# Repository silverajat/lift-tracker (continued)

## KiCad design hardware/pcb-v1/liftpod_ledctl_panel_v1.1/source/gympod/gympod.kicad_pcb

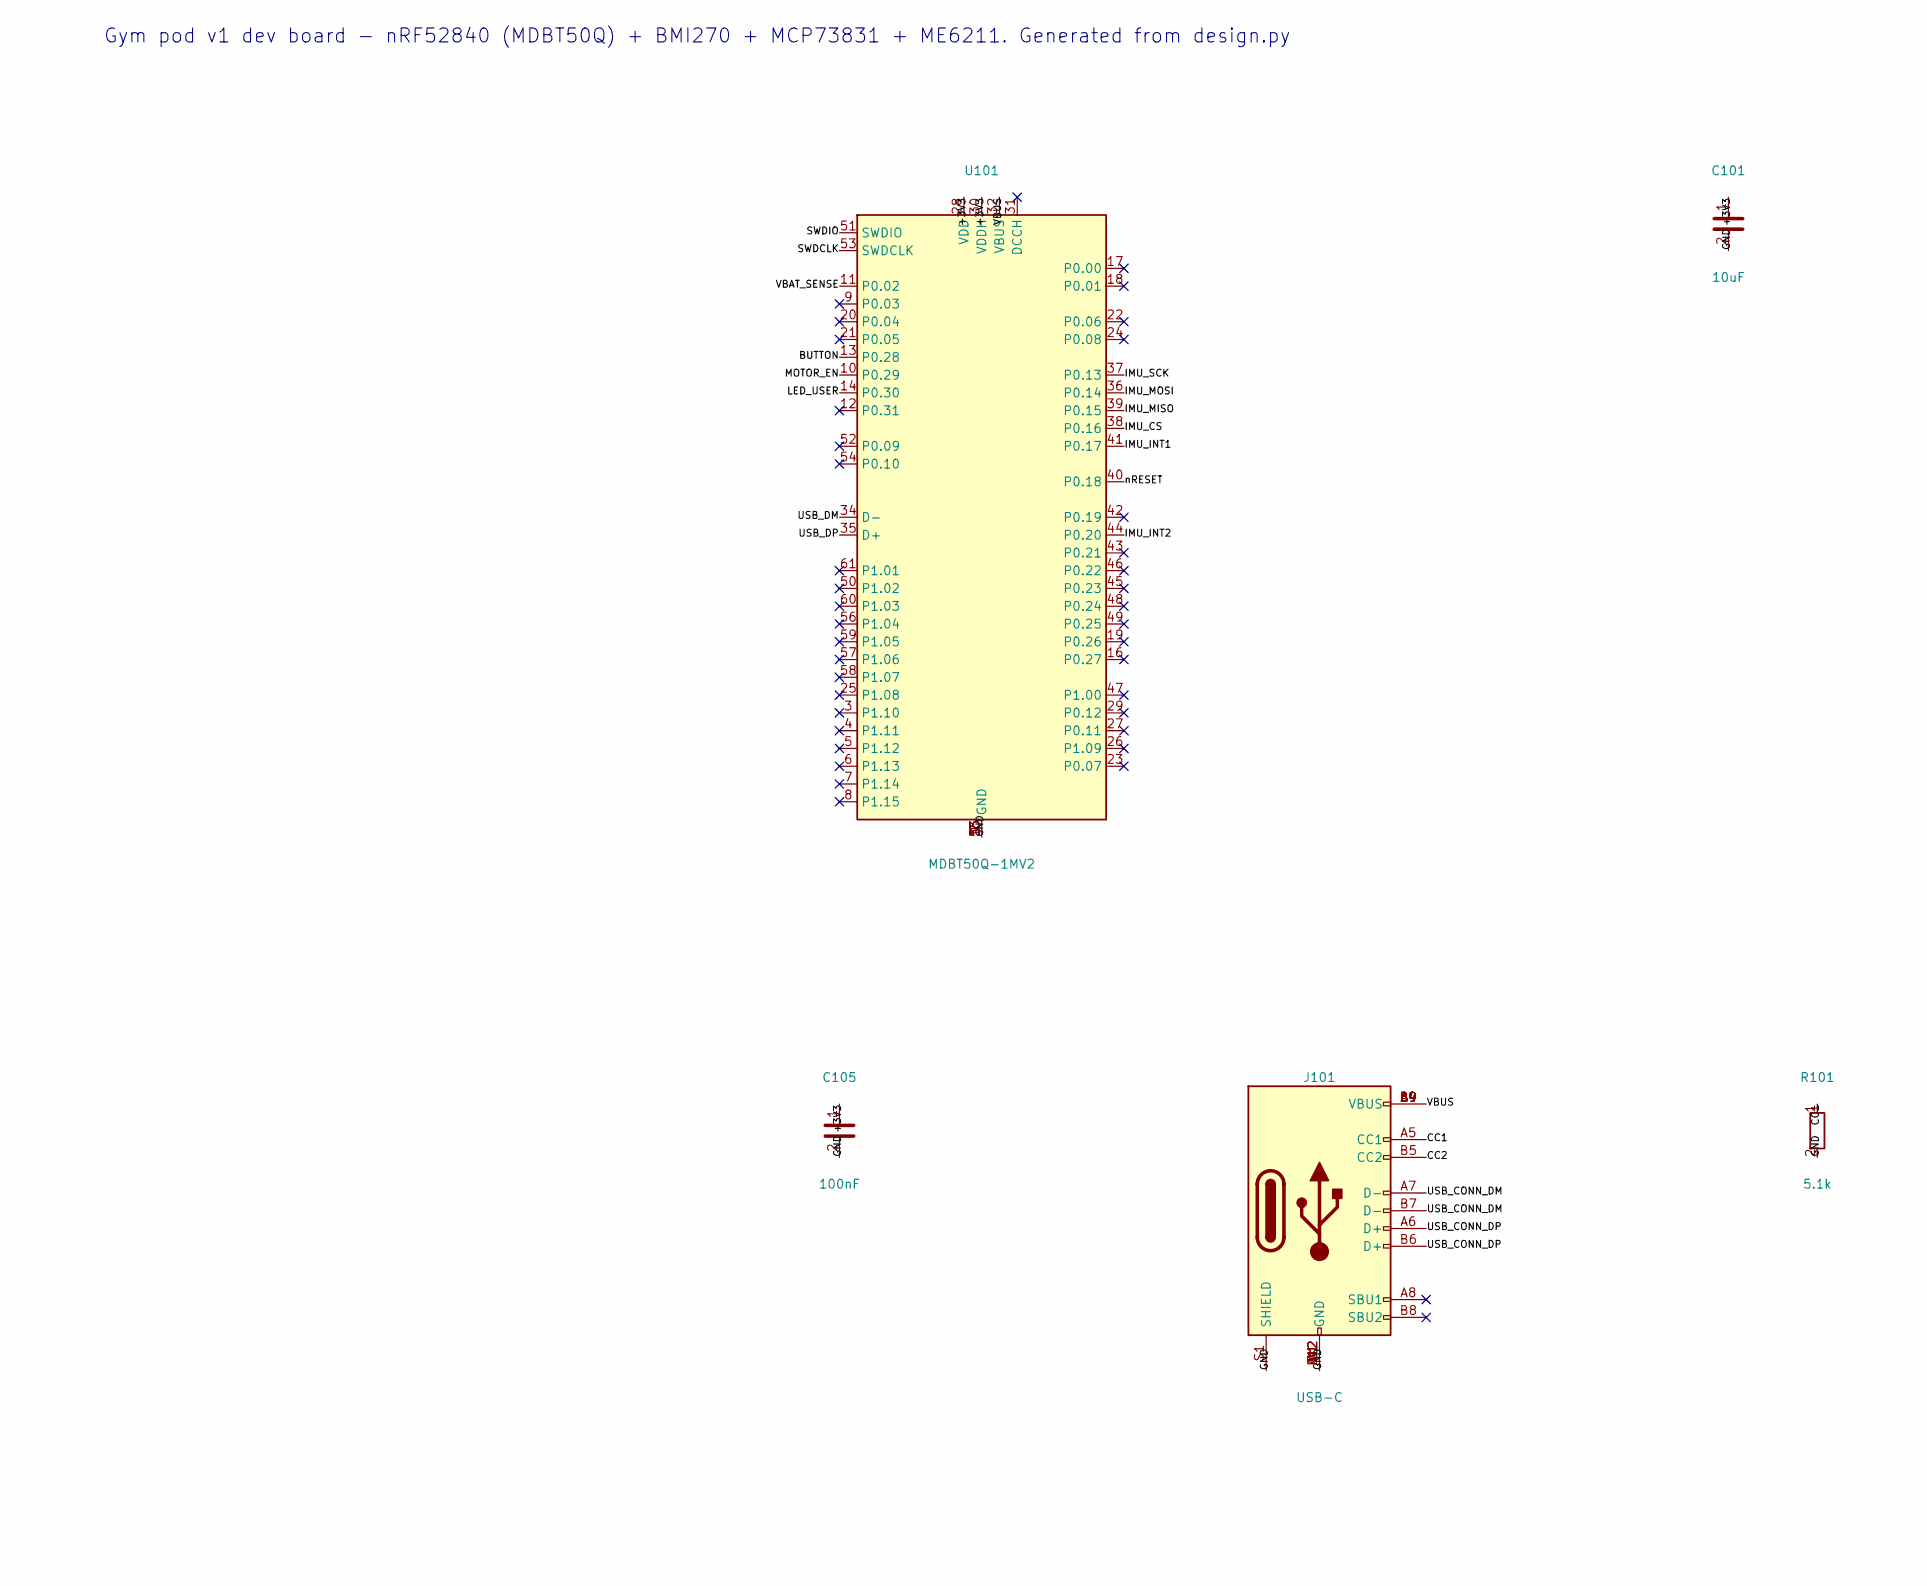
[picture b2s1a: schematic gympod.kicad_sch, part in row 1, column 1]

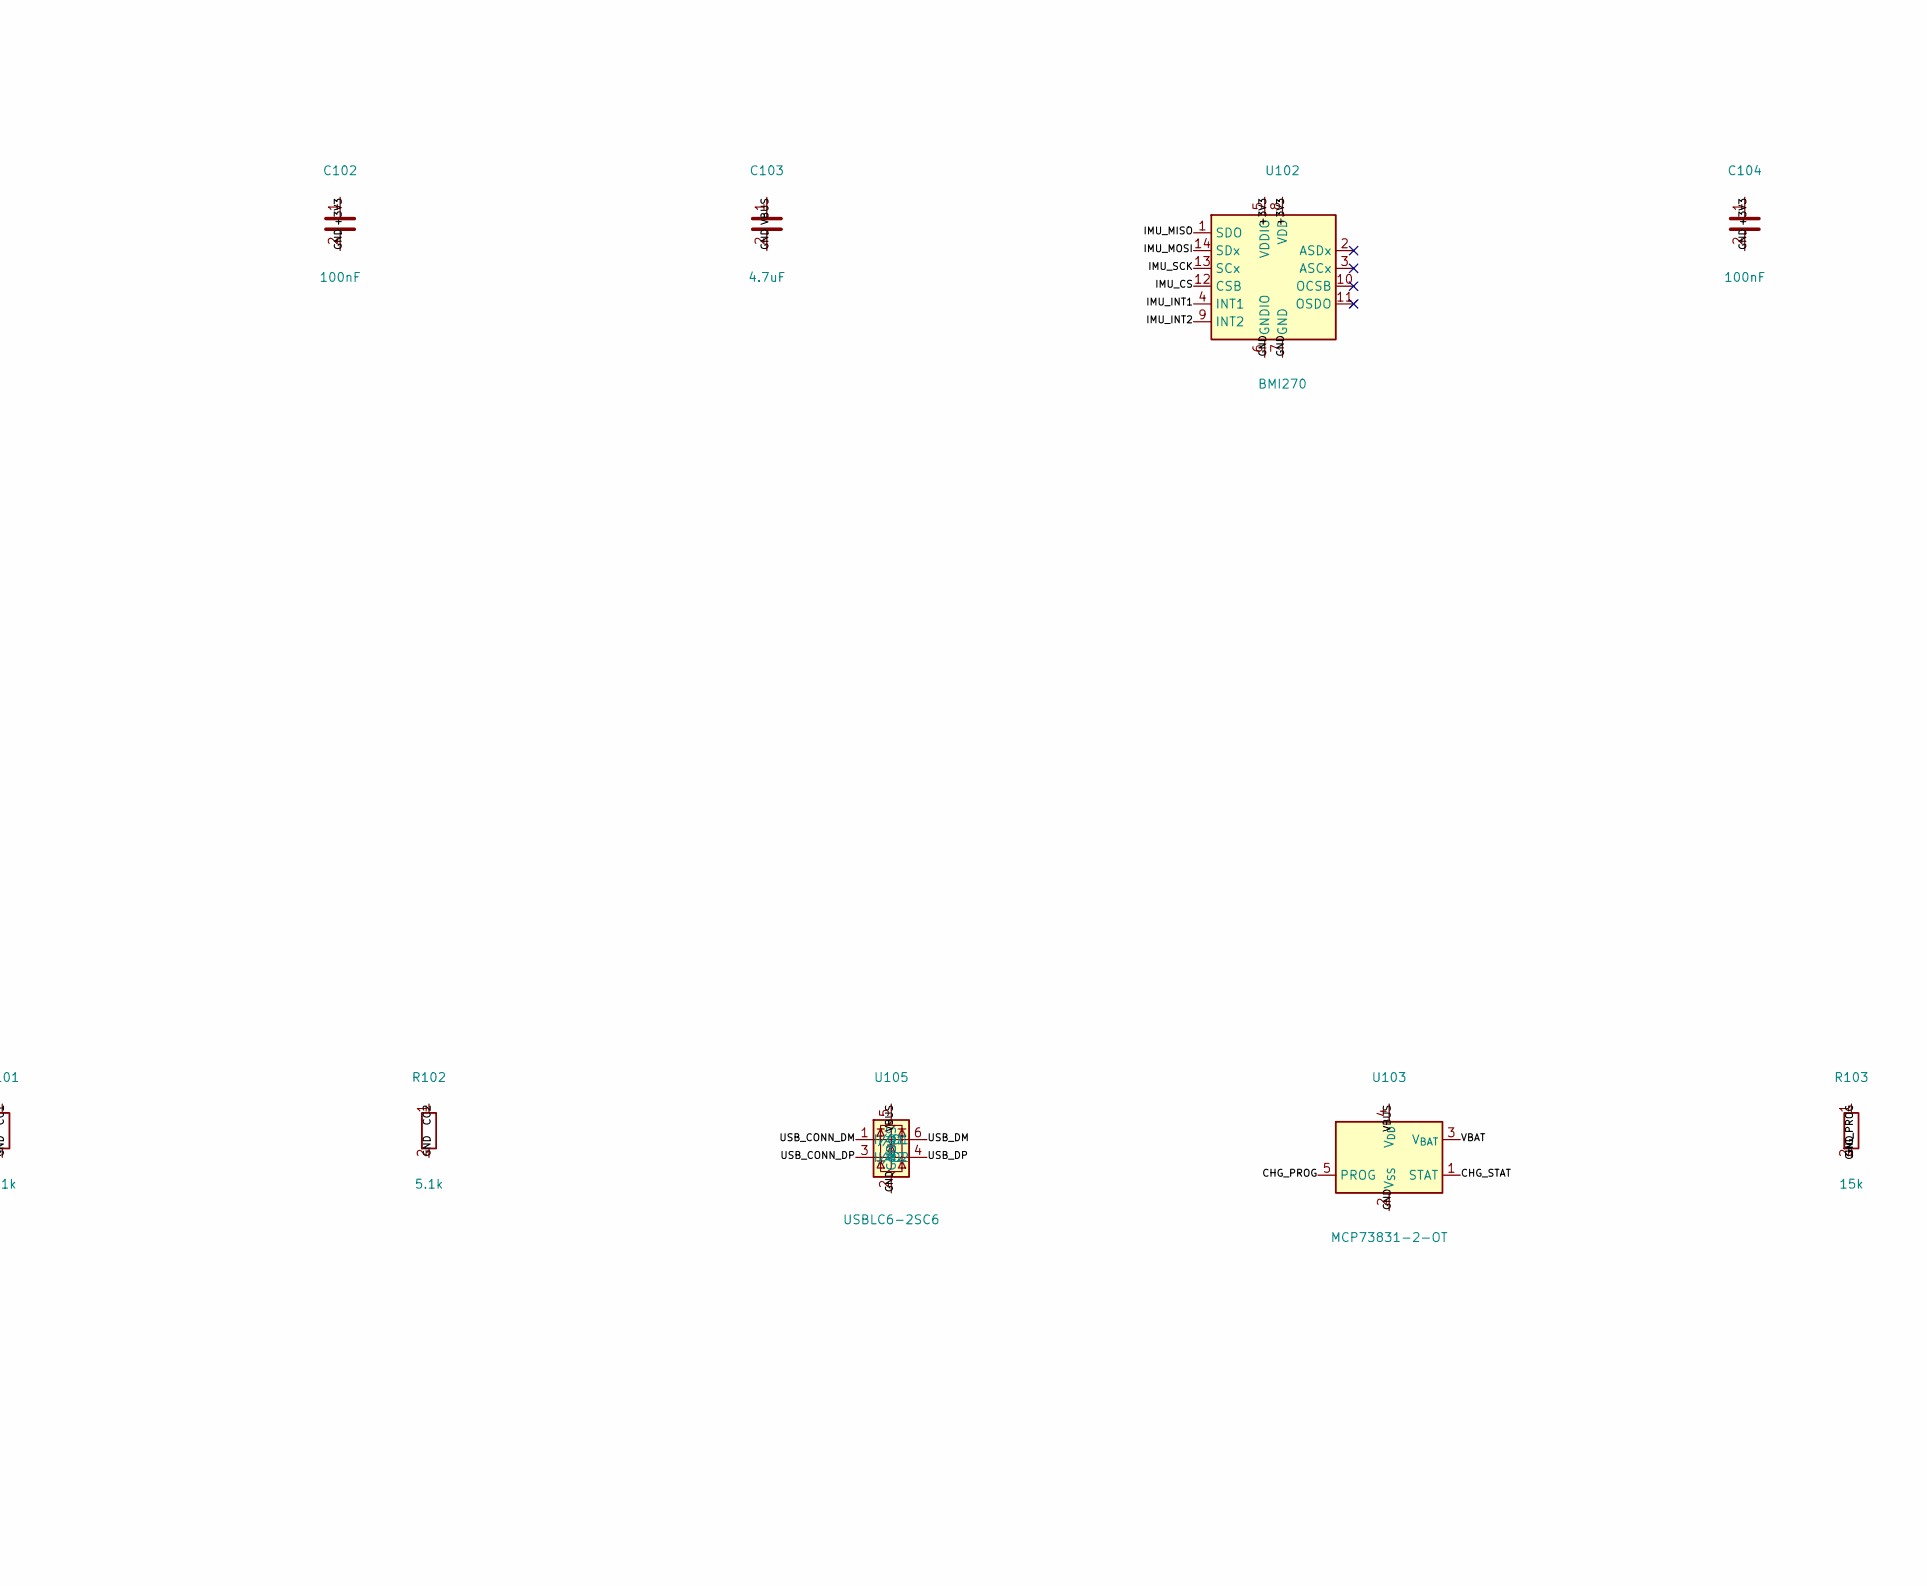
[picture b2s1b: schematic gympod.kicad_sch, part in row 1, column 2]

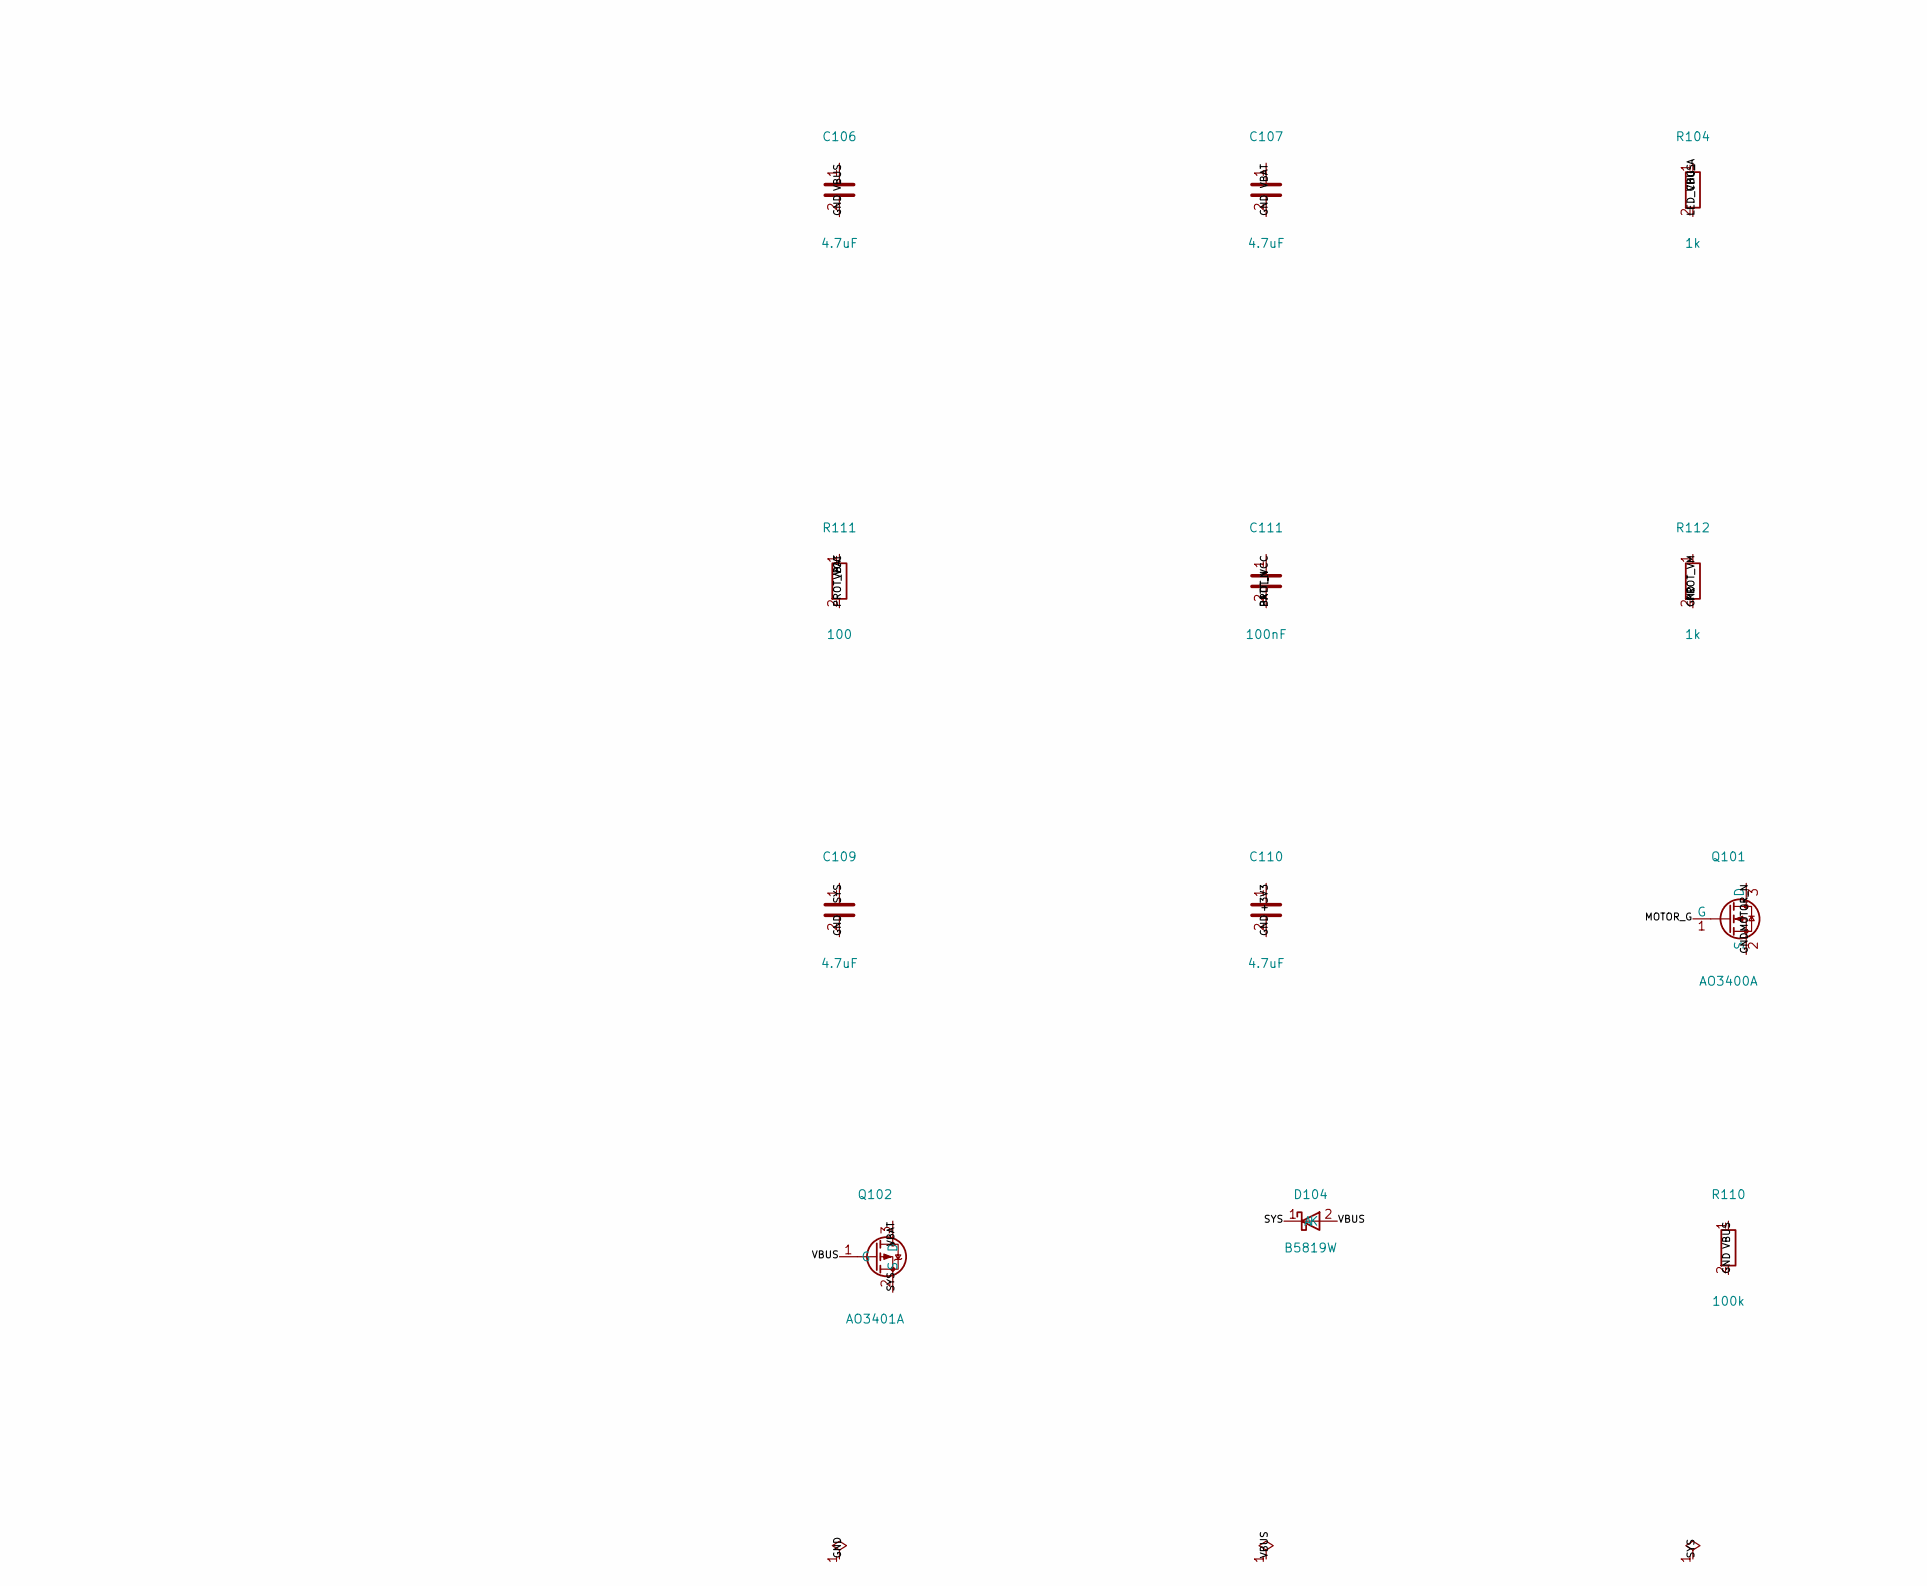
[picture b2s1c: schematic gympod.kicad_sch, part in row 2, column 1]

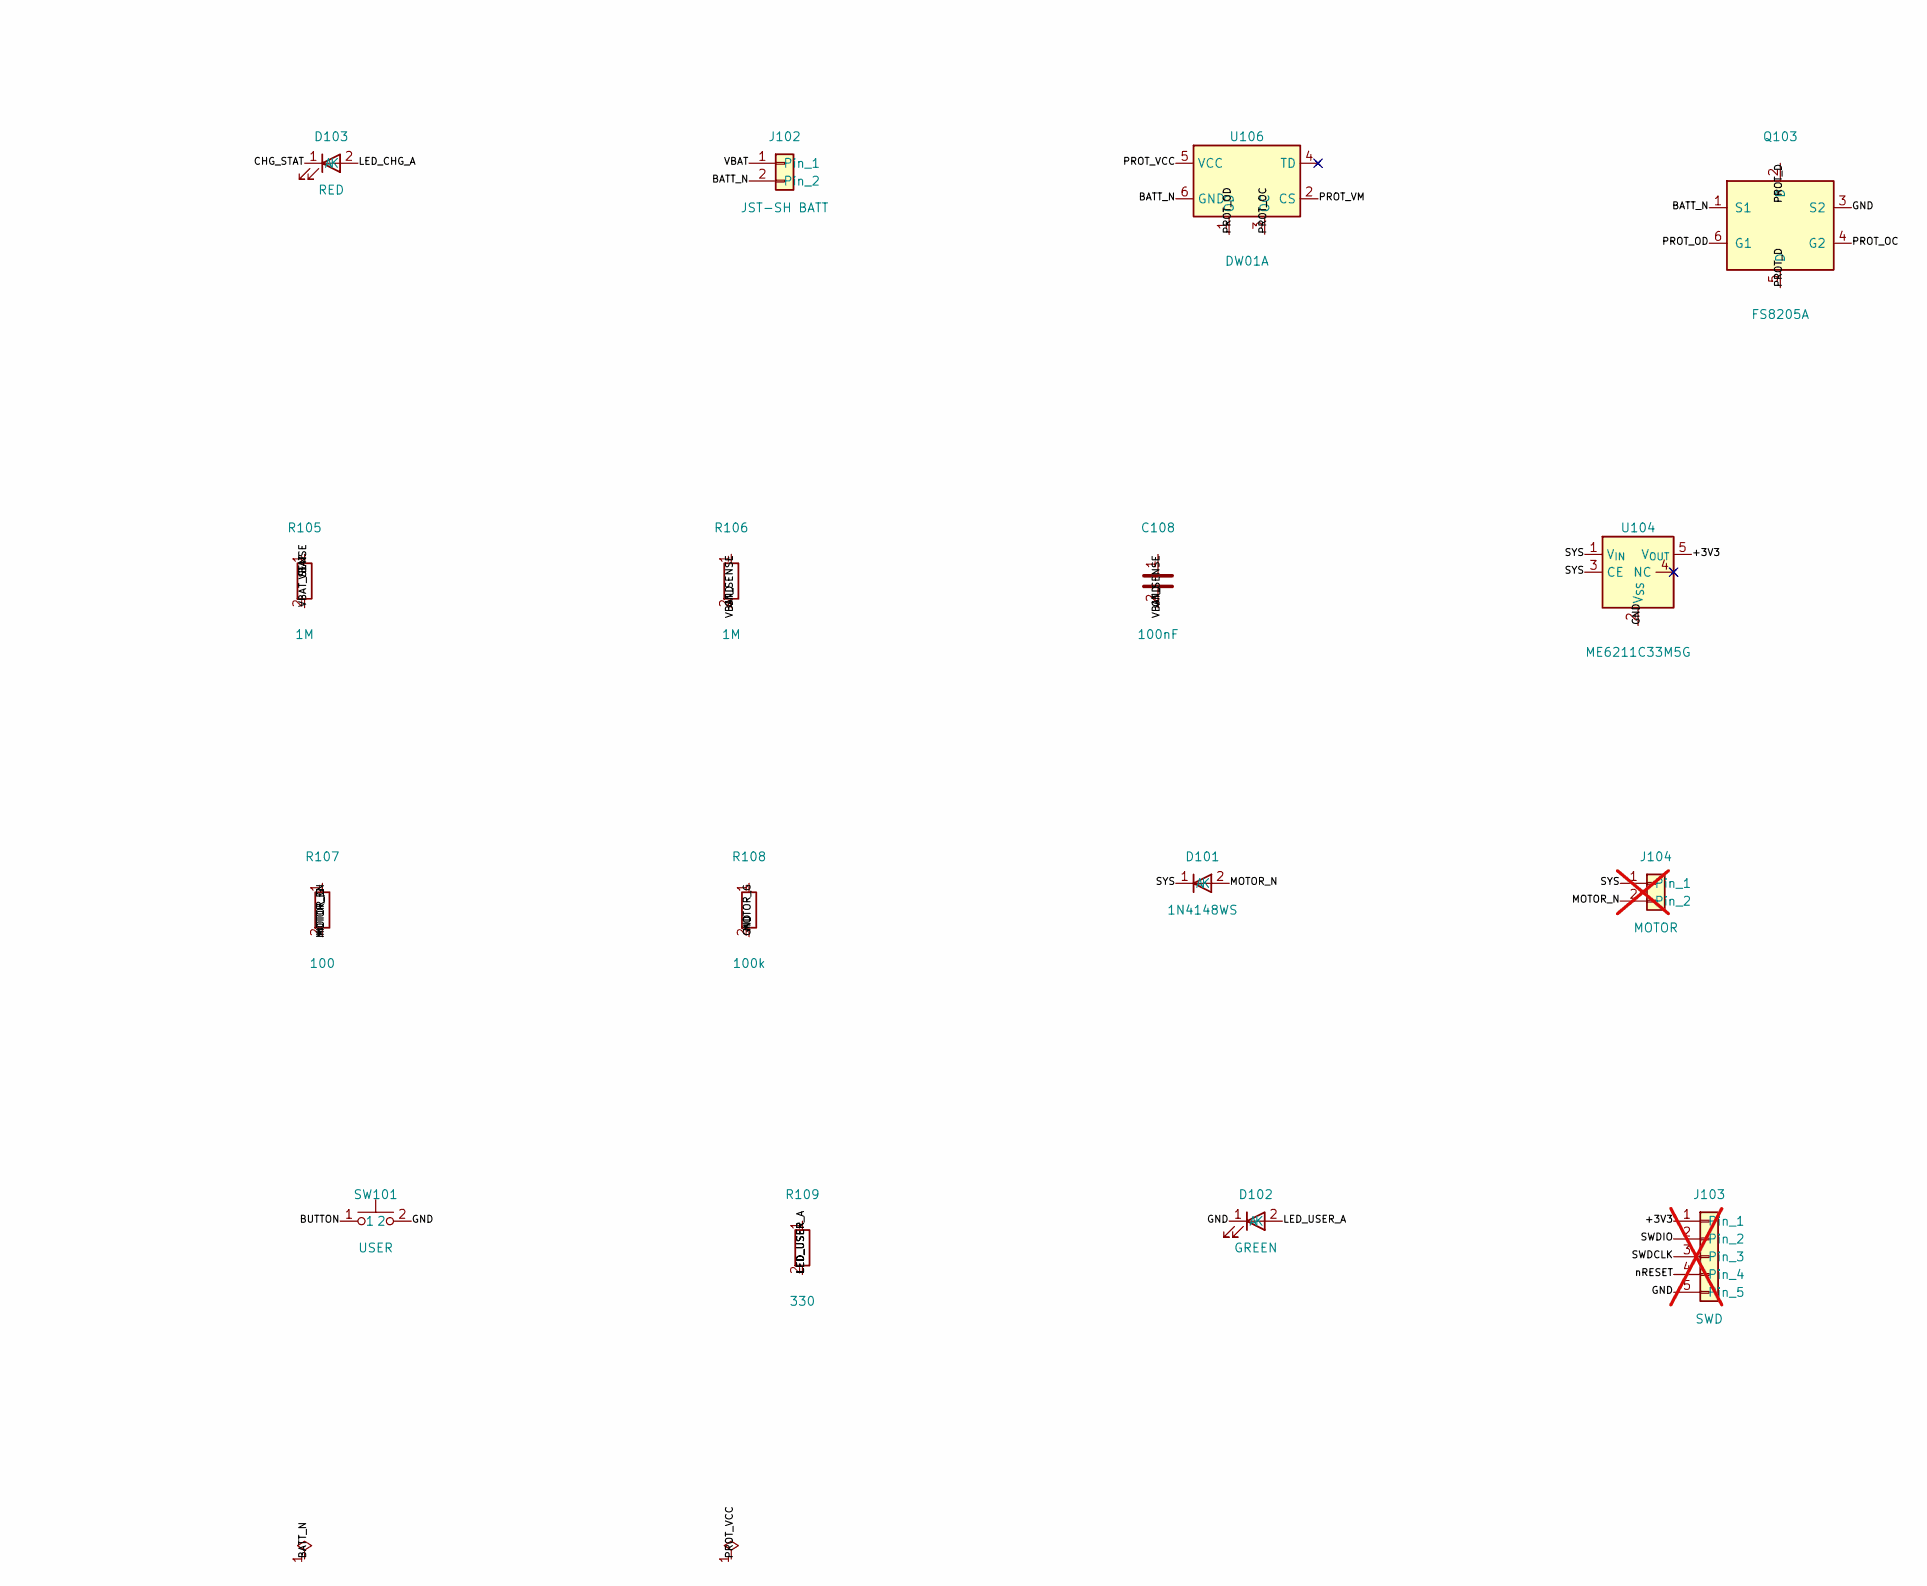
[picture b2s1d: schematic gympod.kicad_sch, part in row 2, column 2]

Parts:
C101: 10uF; C_0603_1608Metric; LCSC C19702
C102, C104, C105, C108, C111: 100nF; C_0603_1608Metric; LCSC C14663
C103, C106, C107, C109, C110: 4.7uF; C_0603_1608Metric; LCSC C19666
D101: 1N4148WS; D_SOD-323; LCSC C2128
D102: GREEN; LED_0603_1608Metric; LCSC C72043
D103: RED; LED_0603_1608Metric; LCSC C2286
D104: B5819W; D_SOD-123; LCSC C8598
J101: USB-C; USB_C_Receptacle_HRO_TYPE-C-31-M-12; LCSC C165948
J102: JST-SH BATT; JST_SH_SM02B-SRSS-TB_1x02-1MP_P1.00mm_Horizontal; LCSC C160402
J103: SWD; PinHeader_1x05_P1.27mm_Vertical; not fitted
J104: MOTOR; PinHeader_1x02_P2.00mm_Vertical_SMD_Pin1Left; not fitted
Q101: AO3400A; SOT-23; LCSC C20917
Q102: AO3401A; SOT-23; LCSC C15127
Q103: FS8205A; SOT-23-6; LCSC C2830320
R101, R102: 5.1k; R_0603_1608Metric; LCSC C23186
R103: 15k; R_0603_1608Metric; LCSC C22809
R104, R112: 1k; R_0603_1608Metric; LCSC C21190
R105, R106: 1M; R_0603_1608Metric; LCSC C22935
R107, R111: 100; R_0603_1608Metric; LCSC C22775
R108, R110: 100k; R_0603_1608Metric; LCSC C25803
R109: 330; R_0603_1608Metric; LCSC C23138
SW101: USER; SW_Push_1P1T_XKB_TS-1187A; LCSC C318884
U101: MDBT50Q-1MV2; Raytac_MDBT50Q; LCSC C5118826
U102: BMI270; Bosch_LGA-14_3x2.5mm_P0.5mm; LCSC C2836813
U103: MCP73831-2-OT; SOT-23-5; LCSC C424093
U104: ME6211C33M5G; SOT-23-5; LCSC C82942
U105: USBLC6-2SC6; SOT-23-6; LCSC C7519
U106: DW01A; SOT-23-6; LCSC C351410

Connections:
/+3V3: C101.1, C102.1, C104.1, C105.1, C110.1, J103.1, U101.28 (VDD), U101.30 (VDDH), U102.5 (VDDIO), U102.8 (VDD), U104.5 (V_{OUT})
/BATT_N: C111.2, J102.2, Q103.1 (S1), U106.6 (GND)
/BUTTON: SW101.1, U101.13 (P0.28)
/CC1: J101.A5 (CC1), R101.1
/CC2: J101.B5 (CC2), R102.1
/CHG_PROG: R103.1, U103.5 (PROG)
/CHG_STAT: D103.1 (K), U103.1 (STAT)
/GND: C101.2, C102.2, C103.2, C104.2, C105.2, C106.2, C107.2, C108.2, C109.2, C110.2, D102.1 (K), J101.A1 (GND), J101.A12 (GND), J101.B1 (GND), J101.B12 (GND), J101.S1 (SHIELD), J103.5, Q101.2 (S), Q103.3 (S2), R101.2, R102.2, R103.2, R106.2, R108.2, R110.2, R112.2, SW101.2, U101.1 (GND), U101.2 (GND), U101.15 (GND), U101.33 (GND), U101.55 (GND), U102.6 (GNDIO), U102.7 (GND), U103.2 (V_{SS}), U104.2 (V_{SS}), U105.2 (GND)
/IMU_CS: U101.38 (P0.16), U102.12 (CSB)
/IMU_INT1: U101.41 (P0.17), U102.4 (INT1)
/IMU_INT2: U101.44 (P0.20), U102.9 (INT2)
/IMU_MISO: U101.39 (P0.15), U102.1 (SDO)
/IMU_MOSI: U101.36 (P0.14), U102.14 (SDx)
/IMU_SCK: U101.37 (P0.13), U102.13 (SCx)
/LED_CHG_A: D103.2 (A), R104.2
/LED_USER: R109.1, U101.14 (P0.30)
/LED_USER_A: D102.2 (A), R109.2
/MOTOR_EN: R107.1, U101.10 (P0.29)
/MOTOR_G: Q101.1 (G), R107.2, R108.1
/MOTOR_N: D101.2 (A), J104.2, Q101.3 (D)
/PROT_D: Q103.2 (D), Q103.5 (D)
/PROT_OC: Q103.4 (G2), U106.3 (OC)
/PROT_OD: Q103.6 (G1), U106.1 (OD)
/PROT_VCC: C111.1, R111.2, U106.5 (VCC)
/PROT_VM: R112.1, U106.2 (CS)
/SWDCLK: J103.3, U101.53 (SWDCLK)
/SWDIO: J103.2, U101.51 (SWDIO)
/SYS: C109.1, D101.1 (K), D104.1 (K), J104.1, Q102.2 (S), U104.1 (V_{IN}), U104.3 (CE)
/USB_CONN_DM: J101.A7 (D-), J101.B7 (D-), U105.1 (I/O1)
/USB_CONN_DP: J101.A6 (D+), J101.B6 (D+), U105.3 (I/O2)
/USB_DM: U101.34 (D-), U105.6 (I/O1)
/USB_DP: U101.35 (D+), U105.4 (I/O2)
/VBAT: C107.1, J102.1, Q102.3 (D), R105.1, R111.1, U103.3 (V_{BAT})
/VBAT_SENSE: C108.1, R105.2, R106.1, U101.11 (P0.02)
/VBUS: C103.1, C106.1, D104.2 (A), J101.A4 (VBUS), J101.A9 (VBUS), J101.B4 (VBUS), J101.B9 (VBUS), Q102.1 (G), R104.1, R110.1, U101.32 (VBUS), U103.4 (V_{DD}), U105.5 (VBUS)
/nRESET: J103.4, U101.40 (P0.18)

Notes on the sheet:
Gym pod v1 dev board - nRF52840 (MDBT50Q) + BMI270 + MCP73831 + ME6211. Generated from design.py

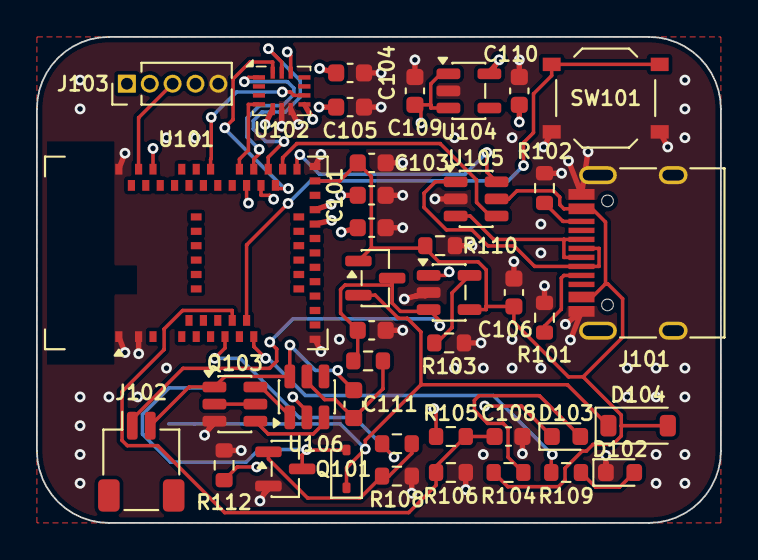
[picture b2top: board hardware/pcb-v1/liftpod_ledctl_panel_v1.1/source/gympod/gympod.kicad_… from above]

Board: 4 copper layers, 38.0 x 27.0 mm, 41 parts (1 on the bottom side), 36 nets.

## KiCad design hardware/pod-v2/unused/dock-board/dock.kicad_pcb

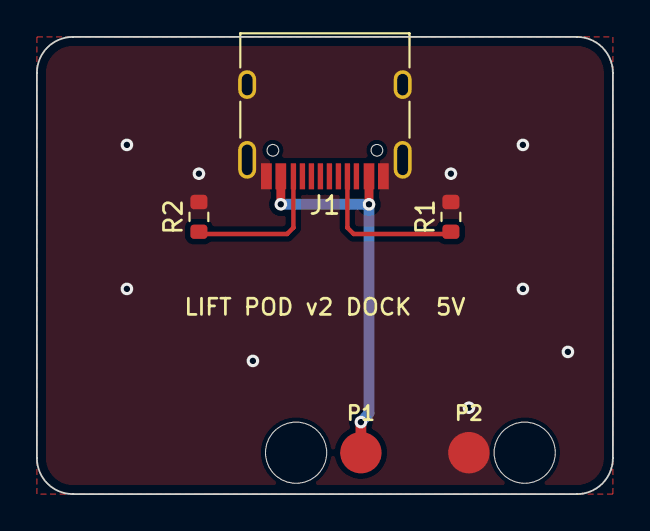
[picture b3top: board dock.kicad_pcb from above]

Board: 2 copper layers, 32.0 x 25.4 mm, 7 parts (0 on the bottom side), 4 nets.

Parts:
H1, H2: (no value)
J1: USB-C; USB_C_Receptacle_HRO_TYPE-C-31-M-12
P1: VIN; Pogo_KH-204065-DZ
P2: GND; Pogo_KH-204065-DZ
R1, R2: 5.1k; R_0603_1608Metric

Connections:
CC1: J1.A5, R1.1
CC2: J1.B5, R2.1
GND: J1.A1, J1.A12, J1.B1, J1.B12, J1.S1, P2.1, R1.2, R2.2
VBUS: J1.A4, J1.A9, J1.B4, J1.B9, P1.1
